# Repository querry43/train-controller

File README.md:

Whistle Board
=============
The Whistle Board is a an inexpensive and easily assembled kit for controlling your model trains with a microcontroller.

Specifications
--------------
 * Supports N and Z scales
 * Control multiple trains with multiple boards
 * Works with your existing train hardware
 * Does not require any modifications to trains or track
 * Does not use PWM which can overheat small motors
 * 700mA per channel
 * Supports both 5V and 3.3V logic

Whistle Board Parts List
------------------------
https://docs.google.com/spreadsheets/d/1KjXTjjhD9g_6WGJ1dTABSkwde-gAP-HaPDzFgPxGlLw/edit#gid=0

Total Cost: ~ $12
 
Output voltage
--------------
This board can be assembled for different model scales by adjusting the value of R3.  Be sure to select the correct value for your scale or you risk damaging your engines.

*Output Voltage Table*

| Scale | Max Output Voltage | R3       |
|-------|--------------------|----------|
| Z     |  8V                | 1.6k ohm |
| N     | 12V                | 820  ohm |

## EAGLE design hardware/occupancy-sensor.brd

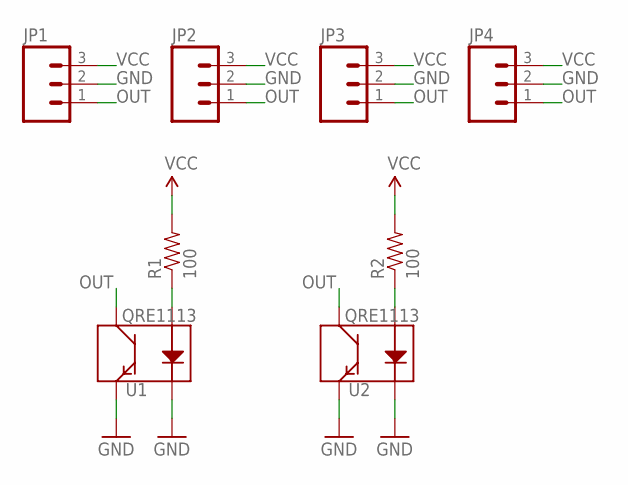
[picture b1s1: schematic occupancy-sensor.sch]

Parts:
JP1, JP2, JP3, JP4: M031X03_NO_SILK; 1X03_NO_SILK
R1, R2: 100; 0603-RES
U1, U2: QRE1113; QRE1113-W

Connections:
GND: JP1.2, JP2.2, JP3.2, JP4.2, U1.2 (K), U1.4 (E), U2.2 (K), U2.4 (E)
unnamed: R1.1, U1.1 (A)
unnamed: R2.1, U2.1 (A)
OUT: JP1.1, JP2.1, JP3.1, JP4.1, U1.3 (C), U2.3 (C)
VCC: JP1.3, JP2.3, JP3.3, JP4.3, R1.2, R2.2

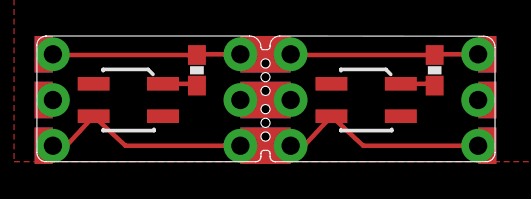
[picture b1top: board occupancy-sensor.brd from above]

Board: 2 copper layers, 25.5 x 7.0 mm, 8 parts (0 on the bottom side), 5 nets.

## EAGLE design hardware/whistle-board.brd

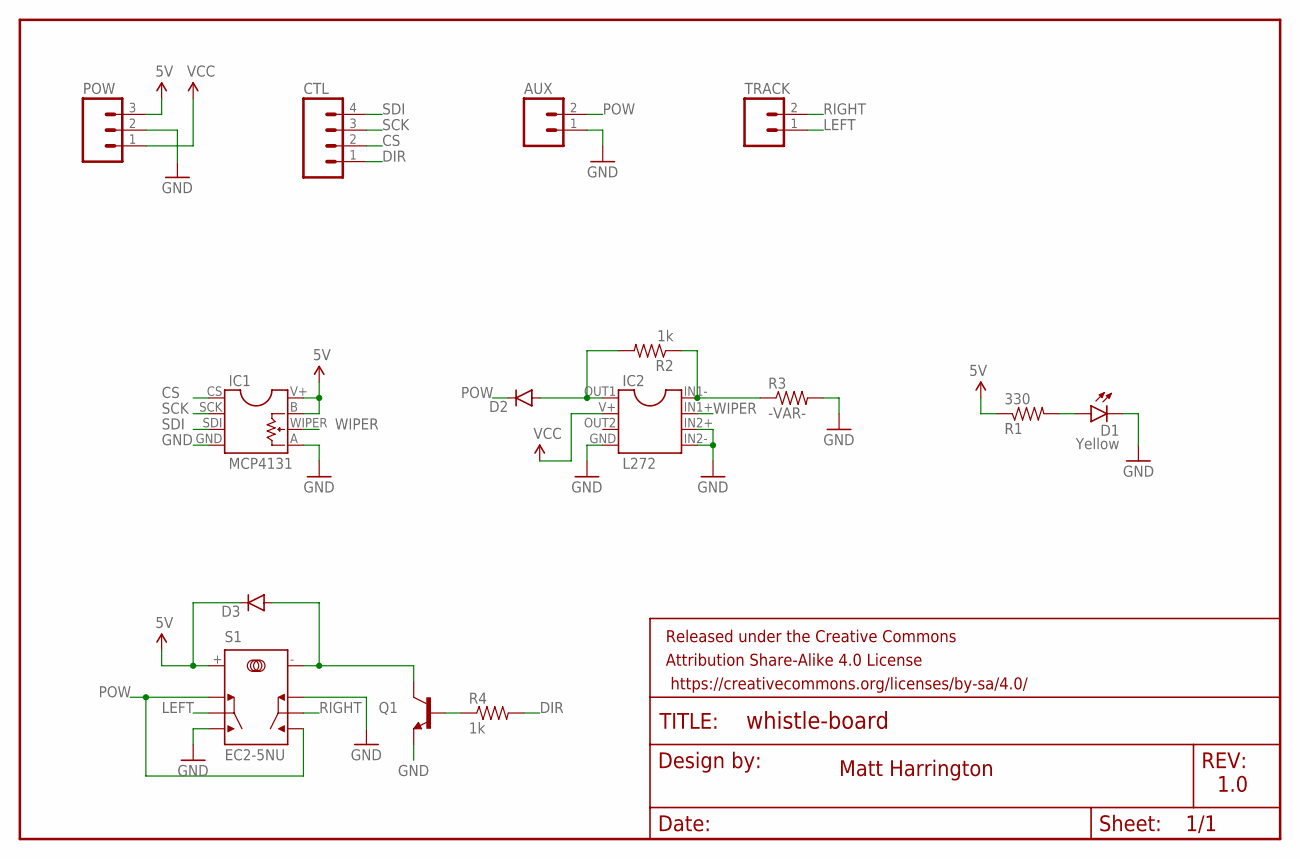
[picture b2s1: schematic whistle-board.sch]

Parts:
AUX: M02PTH; 1X02
CTL: M04PTH; 1X04
D1: Yellow; LED-EDGE
D2: DIODEPTH; DIODE-1N4001
D3: DIODE1N4148; DIODE-1N4148
FRAME1: FRAME-LETTER; CREATIVE_COMMONS
IC1: MCP4131
IC2: L272
POW: M03PTH; 1X03
Q1: TRANSISTOR_NPNTO92; TO-92
R1: 330; AXIAL-0.3
R2, R4: 1k; AXIAL-0.3
R3: -VAR-; AXIAL-0.3
S1: EC2-5NU
TRACK: M02PTH; 1X02

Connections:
5V: D3.C, IC1.B, IC1.V+, POW.3, R1.P$1 (1), S1.+
CS: CTL.2, IC1.CS
DIR: CTL.1, R4.P$2 (2)
GND: AUX.1, D1.C, IC1.A, IC1.GND, IC2.GND, IC2.IN2+, IC2.IN2-, POW.2, Q1.1 (E), R3.P$2 (2), S1.NC2, S1.NO1
LEFT: S1.COM1, TRACK.1
unnamed: D3.A, Q1.3 (C), S1.-
unnamed: Q1.2 (B), R4.P$1 (1)
unnamed: IC2.IN1-, R2.P$1 (1), R3.P$1 (1)
unnamed: D2.A, IC2.OUT1, R2.P$2 (2)
unnamed: D1.A, R1.P$2 (2)
POW: AUX.2, D2.C, S1.NC1, S1.NO2
RIGHT: S1.COM2, TRACK.2
SCK: CTL.3, IC1.SCK
SDI: CTL.4, IC1.SDI
VCC: IC2.V+, POW.1
WIPER: IC1.WIPER, IC2.IN1+

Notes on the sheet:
Matt Harrington
1.0

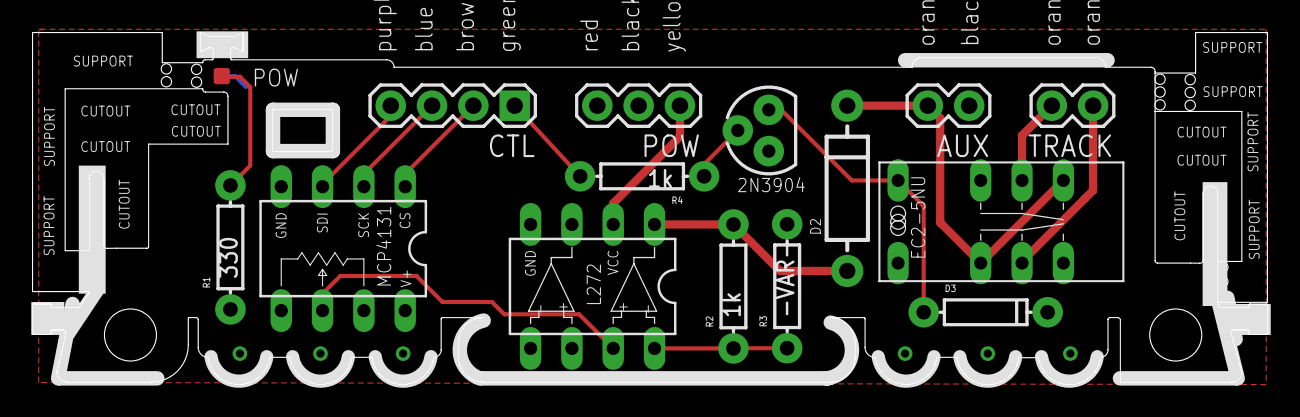
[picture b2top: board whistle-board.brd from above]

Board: 2 copper layers, 75.9 x 21.7 mm, 16 parts (1 on the bottom side), 16 nets.

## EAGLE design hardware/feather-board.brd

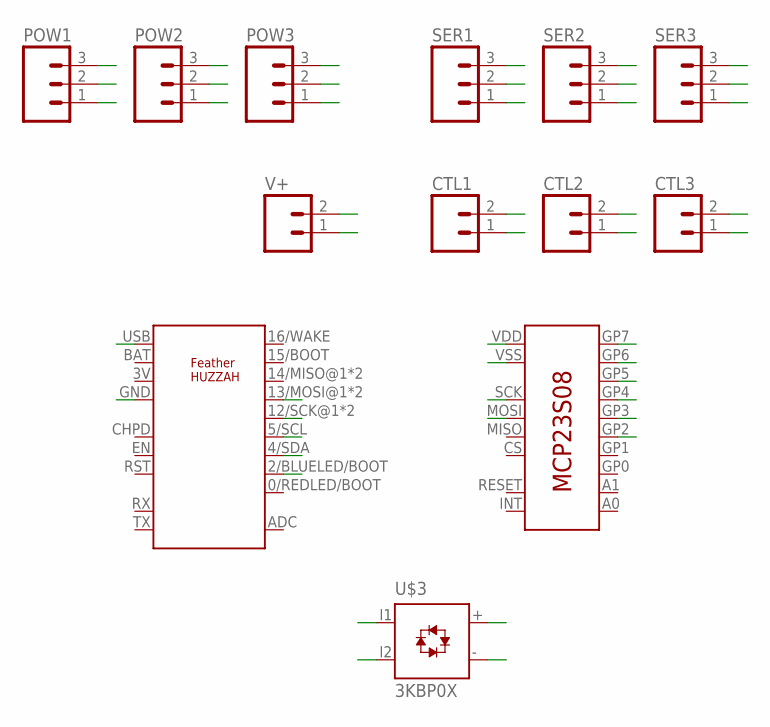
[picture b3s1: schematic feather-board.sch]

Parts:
CTL1, CTL2, CTL3: M021X02_NO_SILK; 1X02_NO_SILK
POW1, POW2, POW3: M031X03_NO_SILK; 1X03_NO_SILK
SER1, SER2, SER3: M031X03_NO_SILK; 1X03_NO_SILK
U$1: ADAFRUITFEATHER
U$2: MCP23S08
U$3: 3KBP0X
V+: M025MM; SCREWTERMINAL-5MM-2

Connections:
CS1: SER1.1, U$1.2/BLUELED/BOOT (2)
CS2: SER2.1, U$1.5/SCL (5)
CS3: SER3.1, U$1.4/SDA (4)
DIR1: CTL1.1, U$2.GP4
DIR2: CTL2.1, U$2.GP3
DIR3: CTL3.1, U$2.GP2
EN1: CTL1.2, U$2.GP5
EN2: CTL2.2, U$2.GP6
EN3: CTL3.2, U$2.GP7
GND: POW1.2, POW2.2, POW3.2, U$1.GND, U$2.VSS, U$3.-
I1: U$3.I1, V+.2
I2: U$3.I2, V+.1
MOSI: SER1.3, SER2.3, SER3.3, U$1.13/MOSI@1 (13), U$1.13/MOSI@2 (13), U$2.MOSI
SCK: SER1.2, SER2.2, SER3.2, U$1.12/SCK@1 (12), U$1.12/SCK@2 (12), U$2.SCK
V5: POW1.1, POW2.1, POW3.1, U$1.USB, U$2.VDD
V+: POW1.3, POW2.3, POW3.3, U$3.+

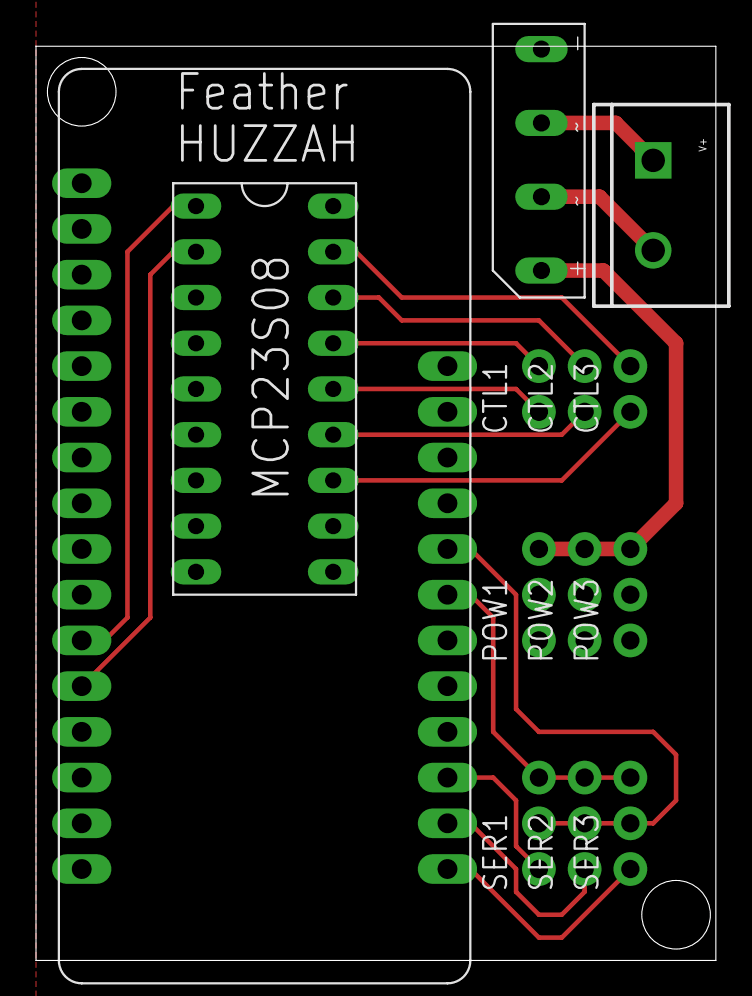
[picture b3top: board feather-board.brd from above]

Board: 2 copper layers, 37.8 x 50.8 mm, 13 parts (0 on the bottom side), 16 nets.

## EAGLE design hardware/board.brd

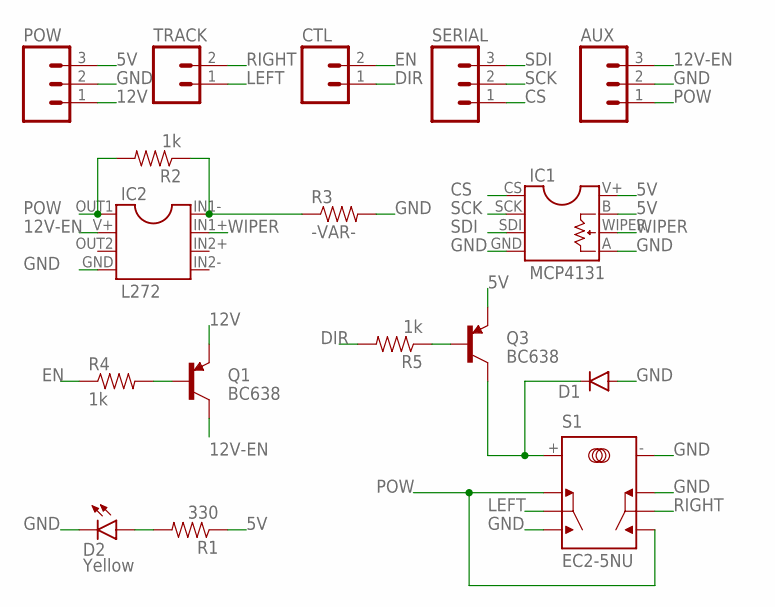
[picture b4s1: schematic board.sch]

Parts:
AUX: M03PTH; 1X03
CTL: M02PTH; 1X02
D1: DIODE1N4148; DIODE-1N4148
D2: Yellow; LED-EDGE
IC1: MCP4131
IC2: L272
POW: M03PTH; 1X03
Q1, Q3: BC638; TO-92
R1: 330; AXIAL-0.3
R2, R4, R5: 1k; AXIAL-0.3
R3: -VAR-; AXIAL-0.3
S1: EC2-5NU
SERIAL: M03PTH; 1X03
TRACK: M02PTH; 1X02

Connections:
5V: IC1.B, IC1.V+, POW.3, Q3.1 (E), R1.P$1 (1)
12V: POW.1, Q1.1 (E)
12V-EN: AUX.3, IC2.V+, Q1.3 (C)
CS: IC1.CS, SERIAL.1
DIR: CTL.1, R5.P$2 (2)
EN: CTL.2, R4.P$1 (1)
GND: AUX.2, D1.A, D2.C, IC1.A, IC1.GND, IC2.GND, POW.2, R3.P$2 (2), S1.-, S1.NC2, S1.NO1
LEFT: S1.COM1, TRACK.1
unnamed: Q1.2 (B), R4.P$2 (2)
unnamed: D1.C, Q3.3 (C), S1.+
unnamed: IC2.IN1-, R2.P$1 (1), R3.P$1 (1)
unnamed: Q3.2 (B), R5.P$1 (1)
unnamed: D2.A, R1.P$2 (2)
POW: AUX.1, IC2.OUT1, R2.P$2 (2), S1.NC1, S1.NO2
RIGHT: S1.COM2, TRACK.2
SCK: IC1.SCK, SERIAL.2
SDI: IC1.SDI, SERIAL.3
WIPER: IC1.WIPER, IC2.IN1+

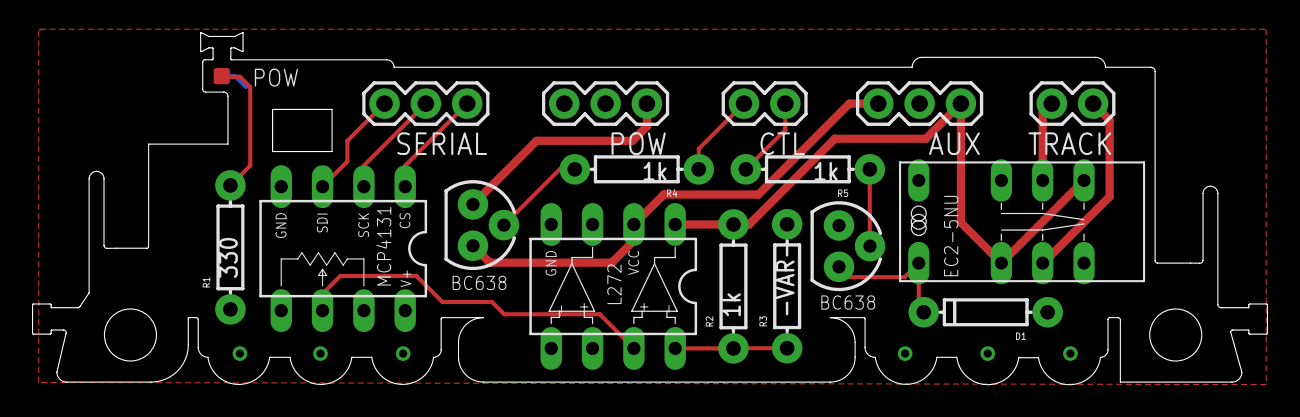
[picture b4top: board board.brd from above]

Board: 2 copper layers, 75.9 x 21.7 mm, 17 parts (1 on the bottom side), 18 nets.

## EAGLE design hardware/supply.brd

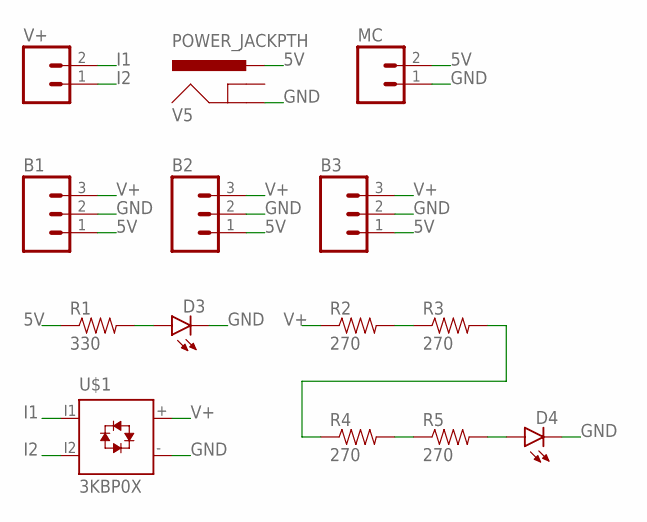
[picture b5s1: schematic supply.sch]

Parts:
B1, B2, B3: M03PTH; 1X03
D3, D4: LED10MM
MC: M02PTH; 1X02
R1: 330; AXIAL-0.3EZ
R2, R3, R4, R5: 270; AXIAL-0.3EZ
U$1: 3KBP0X
V5: POWER_JACKPTH; POWER_JACK_PTH
V+: M025MM; SCREWTERMINAL-5MM-2

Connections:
5V: B1.1, B2.1, B3.1, MC.2, R1.P$1 (1), V5.PWR
GND: B1.2, B2.2, B3.2, D3.C, D4.C, MC.1, U$1.-, V5.GND
I1: U$1.I1, V+.2
I2: U$1.I2, V+.1
unnamed: R2.P$2 (2), R3.P$1 (1)
unnamed: D4.A, R5.P$2 (2)
unnamed: R3.P$2 (2), R4.P$1 (1)
unnamed: D3.A, R1.P$2 (2)
unnamed: R4.P$2 (2), R5.P$1 (1)
V+: B1.3, B2.3, B3.3, R2.P$1 (1), U$1.+

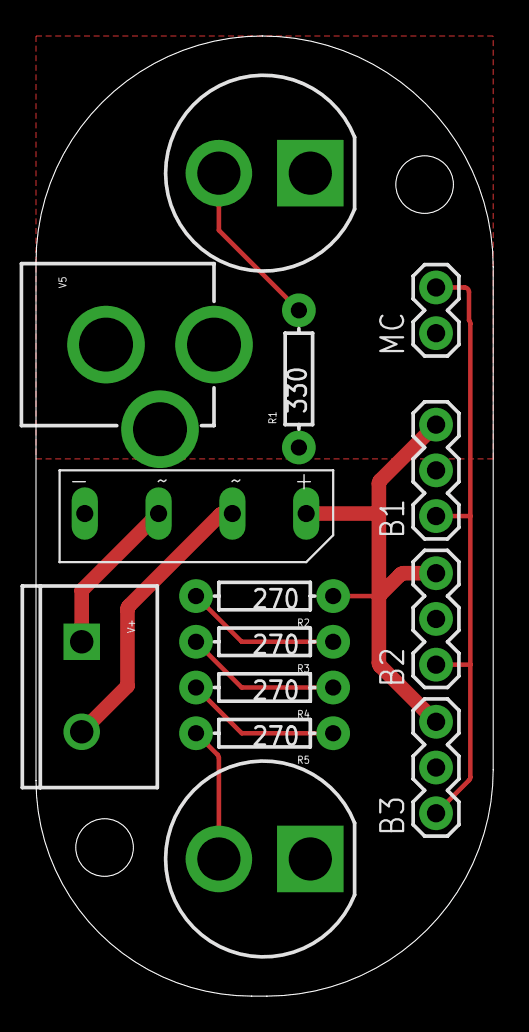
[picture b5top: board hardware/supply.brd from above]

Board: 2 copper layers, 25.4 x 53.3 mm, 14 parts (0 on the bottom side), 10 nets.

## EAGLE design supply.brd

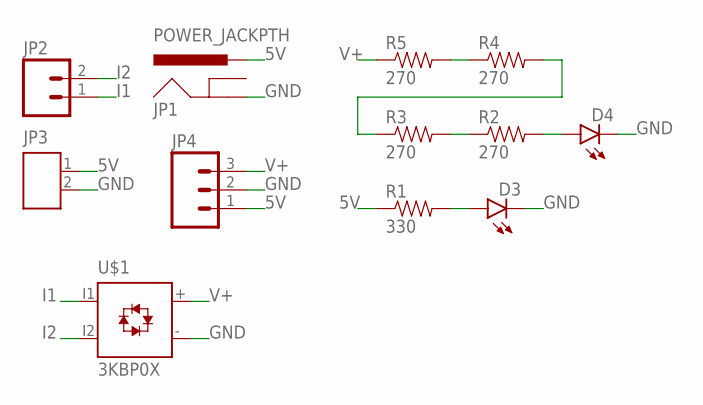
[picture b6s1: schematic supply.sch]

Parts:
D3, D4: LED10MM
JP1: POWER_JACKPTH; POWER_JACK_PTH
JP2: M025MM; SCREWTERMINAL-5MM-2
JP3: M02; JST-2-PTH
JP4: M03LONGPADS; 1X03_LONGPADS
R1: 330; AXIAL-0.3EZ
R2, R3, R4, R5: 270; AXIAL-0.3EZ
U$1: 3KBP0X

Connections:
5V: JP1.PWR, JP3.1, JP4.1, R1.P$1 (1)
GND: D3.C, D4.C, JP1.GND, JP3.2, JP4.2, U$1.-
I1: JP2.1, U$1.I1
I2: JP2.2, U$1.I2
unnamed: R2.P$1 (1), R3.P$2 (2)
unnamed: R3.P$1 (1), R4.P$2 (2)
unnamed: D4.A, R2.P$2 (2)
unnamed: D3.A, R1.P$2 (2)
unnamed: R4.P$1 (1), R5.P$2 (2)
V+: JP4.3, R5.P$1 (1), U$1.+

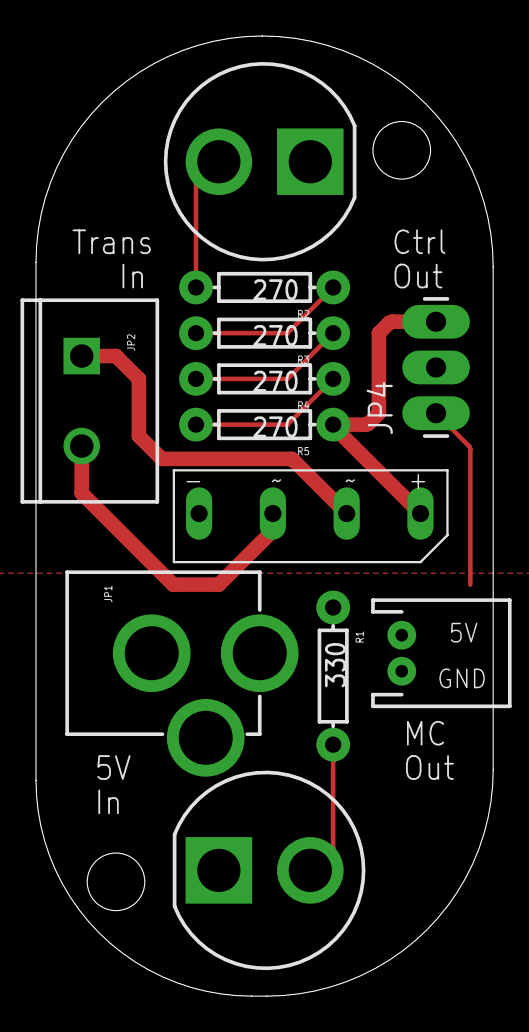
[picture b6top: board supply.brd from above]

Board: 2 copper layers, 25.4 x 53.3 mm, 12 parts (0 on the bottom side), 10 nets.

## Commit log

2015-08-31 :circus_tent: Added .gitattributes & .gitignore files
2015-10-28 fixing digipot wiring
2015-11-11 adding control software
2015-11-11 non-blocking serial communication
2015-12-04 speed rampup improvements
2015-12-28 board v2, adding readme and license
2016-01-16 addressing several items from the bug/feature list
2016-01-17 adding controller board
2016-01-21 getting close to final v2 board, swapping out connectors for molex kk
2016-01-22 update version and documentation
2016-01-23 organizing, adding lua tools
2016-01-23 renaming things, adding images
2016-01-25 adding train control webpage
2016-01-27 working on a different distribution board
2016-01-31 reducing memory footprint
2016-01-31 using ajaxy slider for speed control
2016-01-31 improving defaults
2016-02-01 sliders, reverse, feedback, and memory for 3 train lines
2016-02-21 revisions after the most recent draft was assembled and tested
2016-02-21 automating flash and upload
2016-02-21 slider improvements
2016-02-21 reorganizing makefile(s)
2016-02-21 adding direction control, limiting to two controllers
2016-02-21 sloppily terminating unused opamp
2016-03-03 reworking train control
2016-03-22 updating to newest versions of external tools
2016-03-22 reworking webserver pages to work with newest tools
2016-03-26 updating interface
2016-03-29 using webserver inline functions
2016-03-29 updating javascript
2016-04-01 updating webserver version, few other things
2016-04-03 using bootstrap
    broken due to file size limitations:
    https://github.com/nodemcu/nodemcu-firmware/issues/1164
2016-04-15 adding/fixing diodes, adding silkscreen details
2016-04-24 0.1 pin spacing
2016-04-27 changes after last fab
    - removing opamp short to ground
    - fixing missing silkscreen details
    - small component moves
    - adding support around left railing
2016-05-08 Adding support and ordering (v3)
2016-05-08 begin work on occupancy sensor
2016-05-27 superficial labeling update
2016-05-27 Updating license, annotating schematic, updating images, moving software
2016-06-07 updated arduino software for new board (no enable)
2016-06-27 arduino support for multiple lines
2016-06-27 adding photos
2016-06-28 moar photos
2016-06-28 occupancy sensor improvements
    * rounded corners
    * labels
    * larger pads
    * more perforations
2016-06-29 adding occupancy sensor software, organizing
2016-07-20 updating arduino software, making commands easier and more explicit
2016-10-02 removing HO scale support
2016-10-02 adding ks project image

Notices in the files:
parts and their libraries:
SparkFun-Resistors: Licensing: Creative Commons ShareAlike 4.0 International - https://creativecommons.org/licenses/by-sa/4.0
SparkFun-Aesthetics: Released under the Creative Commons Attribution Share-Alike 4.0 License
SparkFun-Aesthetics: https://creativecommons.org/licenses/by-sa/4.0
